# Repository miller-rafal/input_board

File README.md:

An opto-isolated 8-bit digital input board using the PCF8574 I2C I/O expander chip.
### Features:
* reverse polarity protection
* status LEDs on input terminals
* input resistance 4k7 ohms
* I2C address selectable and pull up-resistors connectable using jumpers
* INT pin exposed

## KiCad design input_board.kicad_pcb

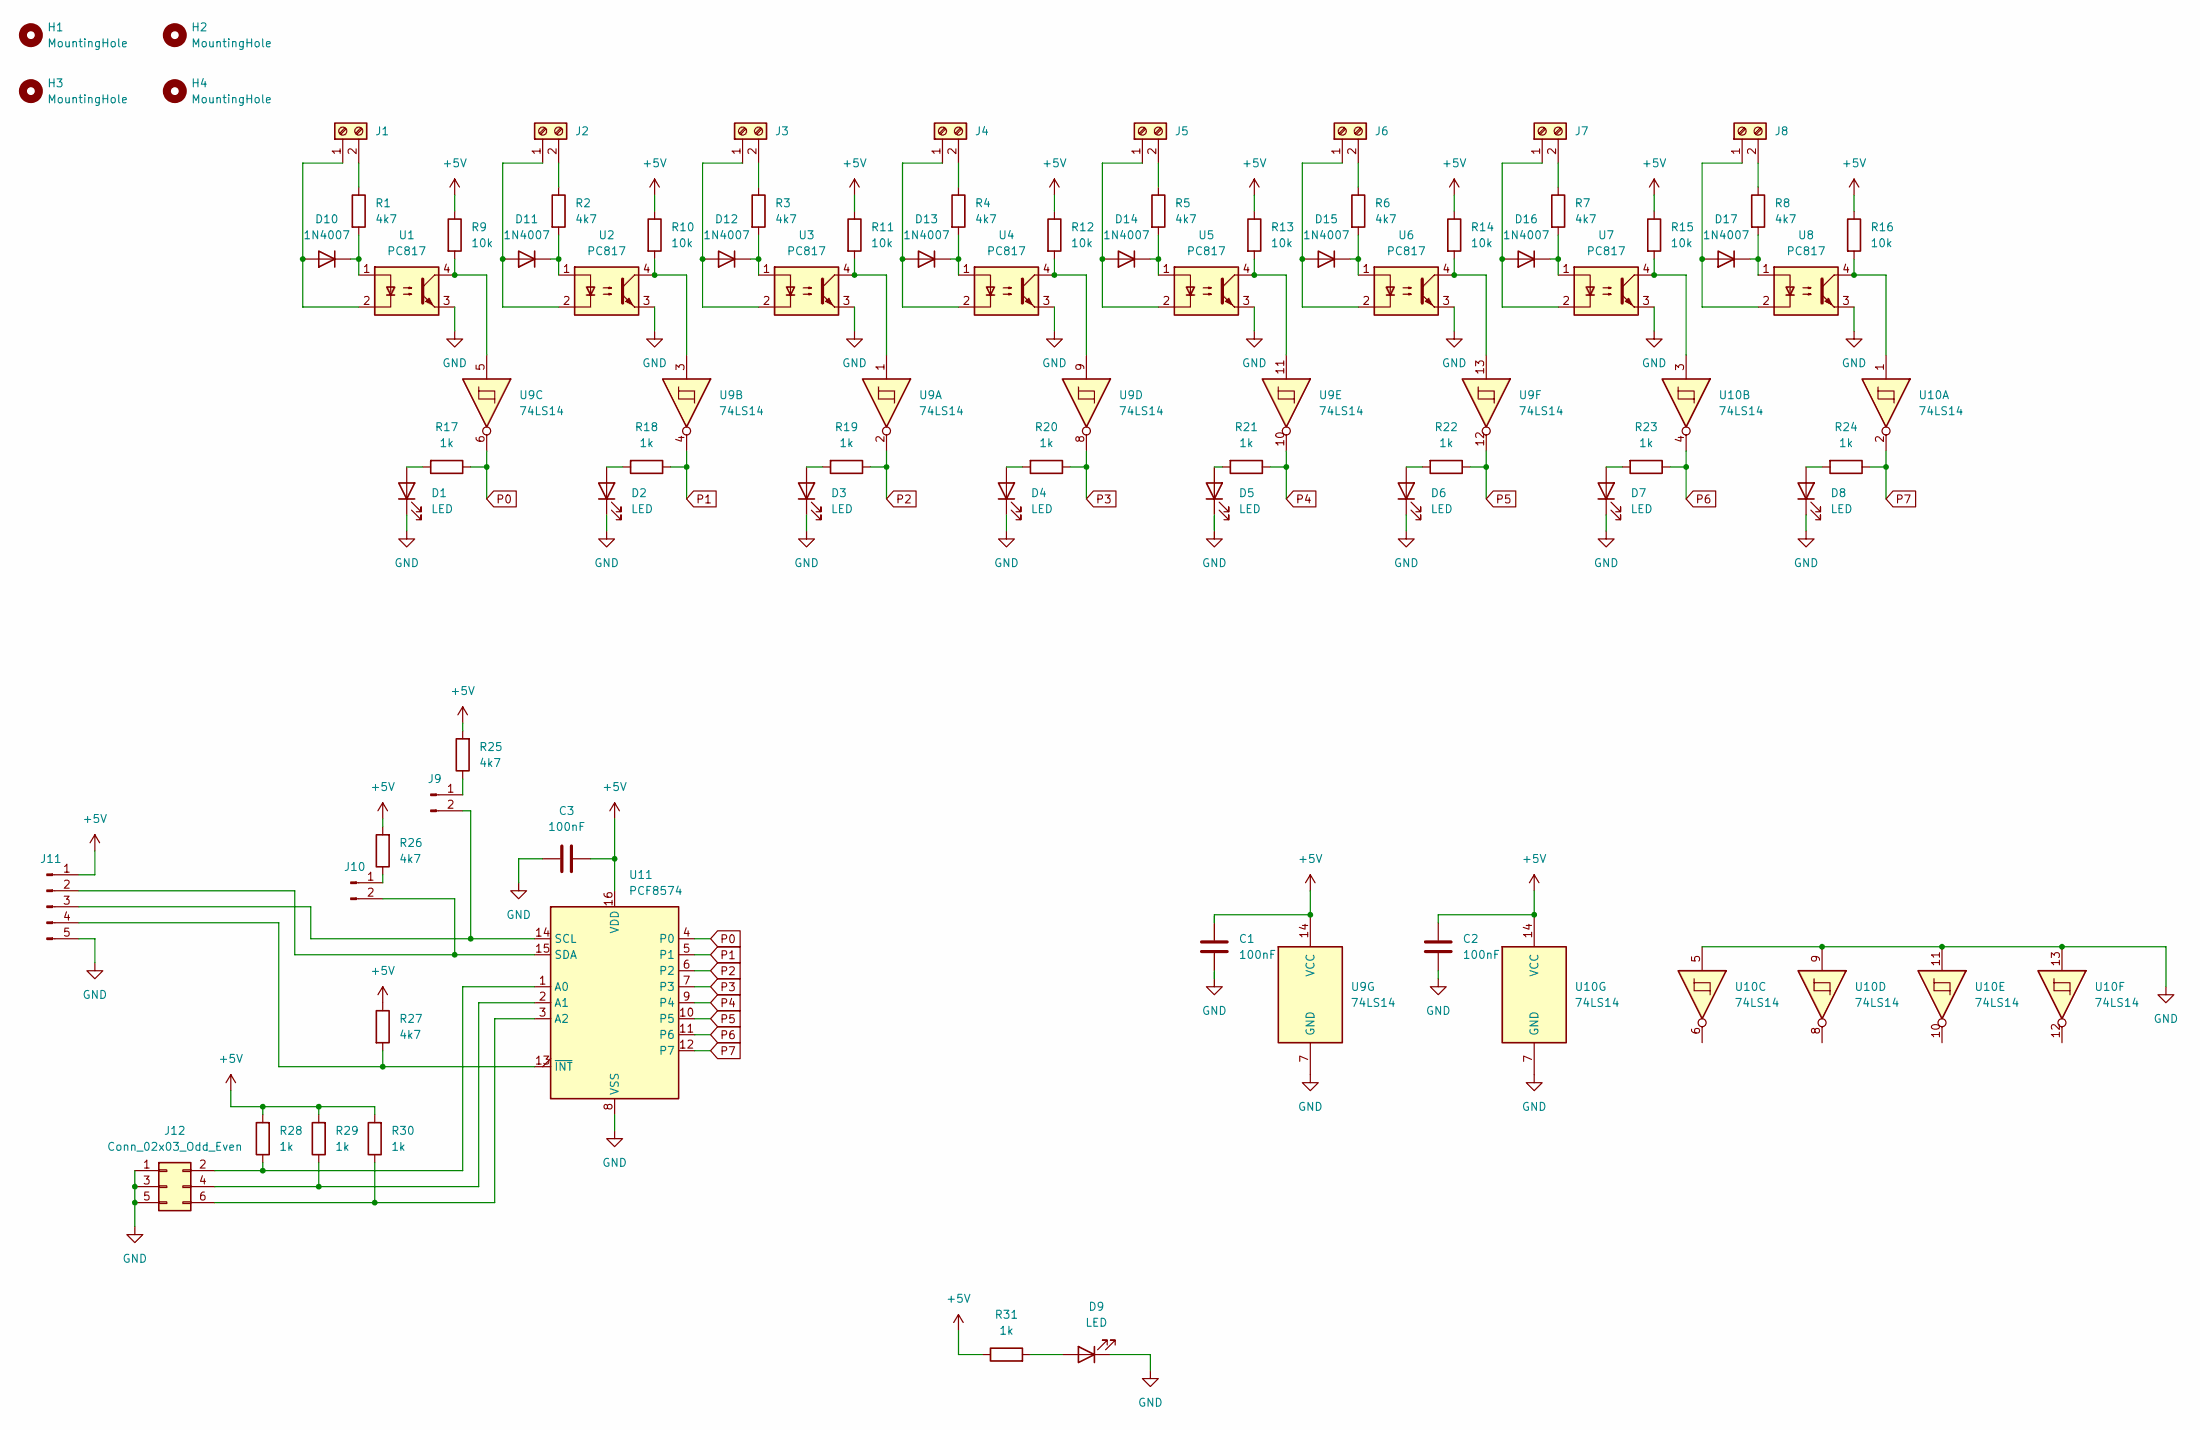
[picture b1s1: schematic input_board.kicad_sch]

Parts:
C1, C2, C3: 100nF; C_Disc_D6.0mm_W2.5mm_P5.00mm
D1, D2, D3, D4, D5, D6, D7, D8, D9: LED; LED_D5.0mm
D10, D11, D12, D13, D14, D15, D16, D17: 1N4007; D_DO-41_SOD81_P10.16mm_Horizontal
H1, H2, H3, H4: MountingHole; MountingHole_2.5mm
J1: DI0; TerminalBlock_bornier-2_P5.08mm
J2: DI1; TerminalBlock_bornier-2_P5.08mm
J3: DI2; TerminalBlock_bornier-2_P5.08mm
J4: DI3; TerminalBlock_bornier-2_P5.08mm
J5: DI4; TerminalBlock_bornier-2_P5.08mm
J6: DI5; TerminalBlock_bornier-2_P5.08mm
J7: DI6; TerminalBlock_bornier-2_P5.08mm
J8: DI7; TerminalBlock_bornier-2_P5.08mm
J9, J10: PinHeader_1x02_P2.54mm_Vertical
J11: PinHeader_1x05_P2.54mm_Vertical
J12: Conn_02x03_Odd_Even; PinHeader_2x03_P2.54mm_Vertical
R1, R2, R3, R4, R5, R6, R7, R8, R25, R26, R27: 4k7; R_Axial_DIN0207_L6.3mm_D2.5mm_P10.16mm_Horizontal
R9, R10, R11, R12, R13, R14, R15, R16: 10k; R_Axial_DIN0207_L6.3mm_D2.5mm_P10.16mm_Horizontal
R17, R18, R19, R20, R21, R22, R23, R24, R28, R29, R30, R31: 1k; R_Axial_DIN0207_L6.3mm_D2.5mm_P10.16mm_Horizontal
U1, U2, U3, U4, U5, U6, U7, U8: PC817; DIP-4_W7.62mm
U9, U10: 74LS14; DIP-14_W7.62mm_Socket
U11: PCF8574; DIP-16_W7.62mm_Socket

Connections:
+5V: C1.1, C2.1, C3.1, J11.1, R9.1, R10.1, R11.1, R12.1, R13.1, R14.1, R15.1, R16.1, R25.2, R26.2, R27.1, R28.2, R29.2, R30.2, R31.1, U9.14 (VCC), U10.14 (VCC), U11.16 (VDD)
GND: C1.2, C2.2, C3.2, D1.1 (K), D2.1 (K), D3.1 (K), D4.1 (K), D5.1 (K), D6.1 (K), D7.1 (K), D8.1 (K), D9.1 (K), J11.5, J12.1, J12.3, J12.5, U1.3, U2.3, U3.3, U4.3, U5.3, U6.3, U7.3, U8.3, U9.7 (GND), U10.5, U10.7 (GND), U10.9, U10.11, U10.13, U11.8 (VSS)
unnamed: D1.2 (A), R17.2
unnamed: D2.2 (A), R18.2
unnamed: D3.2 (A), R19.2
unnamed: D4.2 (A), R20.2
unnamed: D5.2 (A), R21.2
unnamed: D6.2 (A), R22.2
unnamed: D7.2 (A), R23.2
unnamed: D8.2 (A), R24.2
unnamed: D9.2 (A), R31.2
unnamed: D10.2 (A), J1.1, U1.2
unnamed: D10.1 (K), R1.2, U1.1
unnamed: D11.2 (A), J2.1, U2.2
unnamed: D11.1 (K), R2.2, U2.1
unnamed: D12.2 (A), J3.1, U3.2
unnamed: D12.1 (K), R3.2, U3.1
unnamed: D13.2 (A), J4.1, U4.2
unnamed: D13.1 (K), R4.2, U4.1
unnamed: D14.2 (A), J5.1, U5.2
unnamed: D14.1 (K), R5.2, U5.1
unnamed: D15.2 (A), J6.1, U6.2
unnamed: D15.1 (K), R6.2, U6.1
unnamed: D16.2 (A), J7.1, U7.2
unnamed: D16.1 (K), R7.2, U7.1
unnamed: D17.2 (A), J8.1, U8.2
unnamed: D17.1 (K), R8.2, U8.1
unnamed: J1.2, R1.1
unnamed: J2.2, R2.1
unnamed: J3.2, R3.1
unnamed: J4.2, R4.1
unnamed: J5.2, R5.1
unnamed: J6.2, R6.1
unnamed: J7.2, R7.1
unnamed: J8.2, R8.1
unnamed: J9.1, R25.1
unnamed: J10.1, R26.1
unnamed: J10.2, J11.2, U11.15 (SDA)
unnamed: J9.2, J11.3, U11.14 (SCL)
unnamed: J11.4, R27.2, U11.13 (~INT)
unnamed: J12.2, R28.1, U11.1 (A0)
unnamed: J12.4, R29.1, U11.2 (A1)
unnamed: J12.6, R30.1, U11.3 (A2)
unnamed: R9.2, U1.4, U9.5
unnamed: R10.2, U2.4, U9.3
unnamed: R11.2, U3.4, U9.1
unnamed: R12.2, U4.4, U9.9
unnamed: R13.2, U5.4, U9.11
unnamed: R14.2, U6.4, U9.13
unnamed: R15.2, U7.4, U10.3
unnamed: R16.2, U8.4, U10.1
P0: R17.1, U9.6, U11.4 (P0)
P1: R18.1, U9.4, U11.5 (P1)
P2: R19.1, U9.2, U11.6 (P2)
P3: R20.1, U9.8, U11.7 (P3)
P4: R21.1, U9.10, U11.9 (P4)
P5: R22.1, U9.12, U11.10 (P5)
P6: R23.1, U10.4, U11.11 (P6)
P7: R24.1, U10.2, U11.12 (P7)

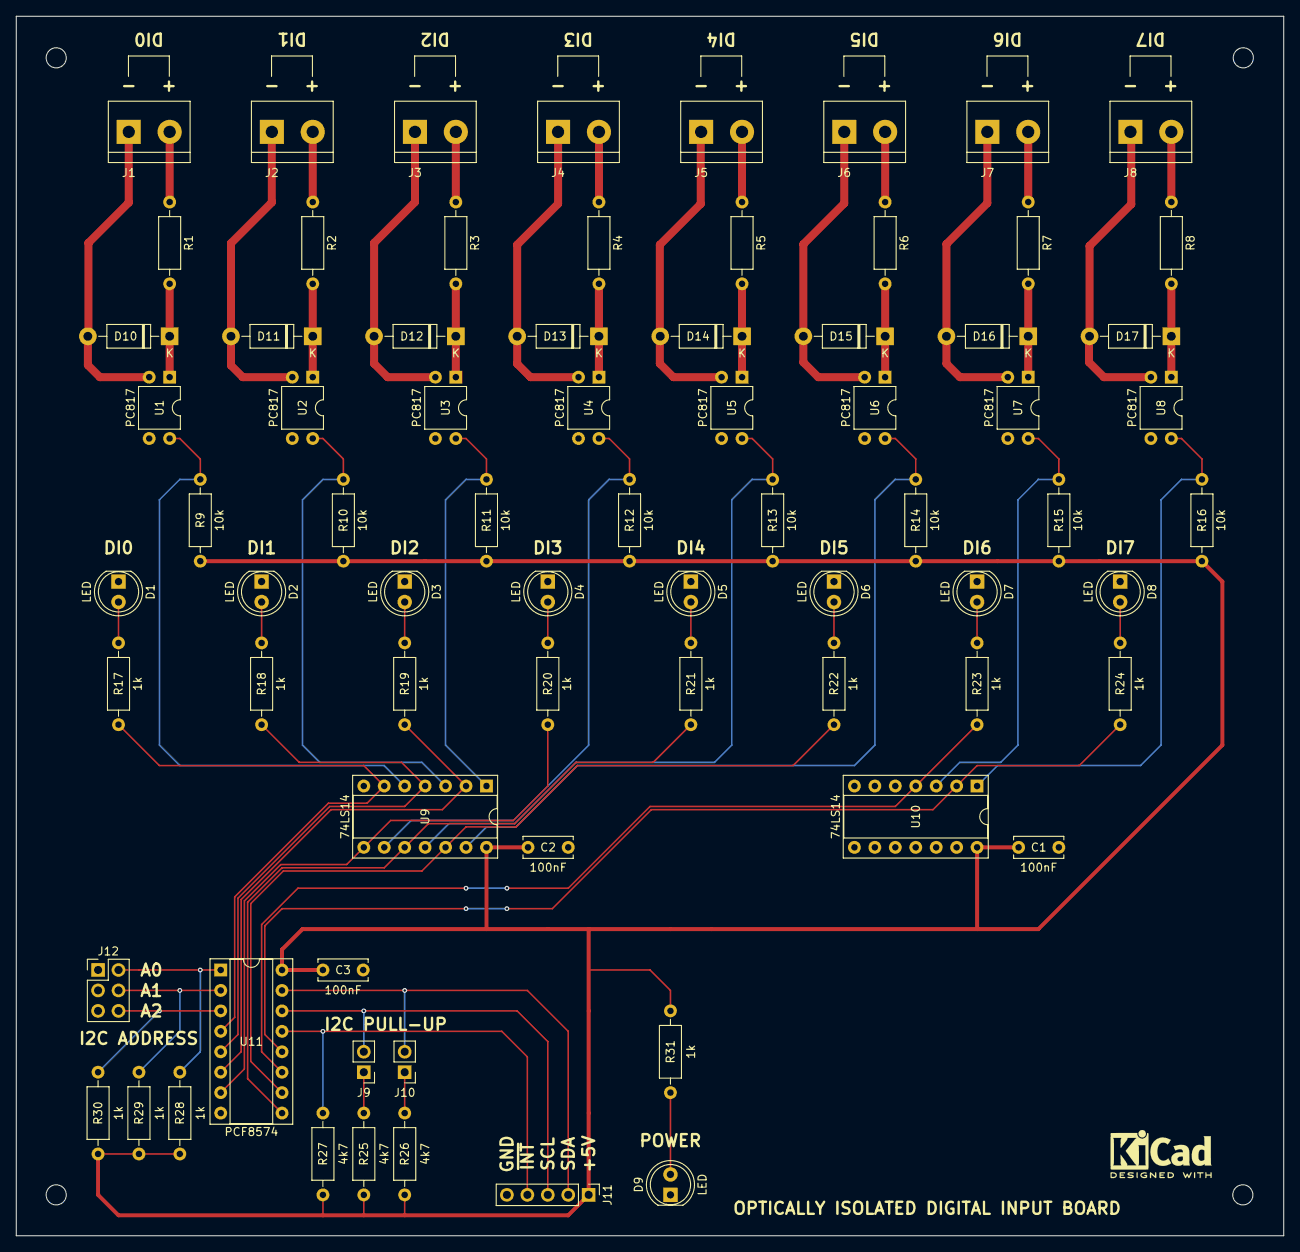
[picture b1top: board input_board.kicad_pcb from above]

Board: 2 copper layers, 157.5 x 151.5 mm, 78 parts (0 on the bottom side), 59 nets.
